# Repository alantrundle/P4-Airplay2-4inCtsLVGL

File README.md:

# P4-Airplay2-4inCtsLVGL
P4 Airplay2 Project featuring 4in TS and Capacitive TS

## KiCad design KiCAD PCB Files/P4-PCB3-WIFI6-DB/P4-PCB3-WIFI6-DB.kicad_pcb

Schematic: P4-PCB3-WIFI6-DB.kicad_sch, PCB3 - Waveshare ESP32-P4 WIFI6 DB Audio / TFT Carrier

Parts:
C1, C2: 220pF; C_0603_1608Metric; LCSC C1603; not fitted
C3, C7: 100uF; C_1206_3216Metric; LCSC C15008
C4: 4.7uF; C_0603_1608Metric; LCSC C19666
C5, C6, C10, C12, C14, C16, C17, C23, C25, C29, C30, C33, C34, C77, C86, C94, C95: 100nF; C_0603_1608Metric; LCSC C14663
C9, C11, C13, C15, C21, C32, C76: 10uF; C_0603_1608Metric; LCSC C19702
C24, C26, C89: 2.2uF; C_0603_1608Metric; LCSC C23630
C27, C28: 2.2nF; C_0603_1608Metric; LCSC C1604
C66, C81, C96: 10uF; C_0805_2012Metric; LCSC C15850
C87, C90, C91: 1uF; C_0603_1608Metric; LCSC C15849
C88: 22uF; C_0805_2012Metric; LCSC C45783
C92, C93: 100pF; C_0603_1608Metric; LCSC C14858
D1: Green LED; LED_0603_1608Metric; LCSC C12624
DS1: FH34SRJ-40S-0.5SH(50); ILI9488_40P_4inch_Checked; MPN FH34SRJ-40S-0.5SH(50); LCSC C506798
H1, H2, H3, H4: MountingHole; MountingHole_3.2mm_M3; not fitted
J2, J3: PJ-320D; HanElectricity_PJ320D_C22459515; LCSC C22459515
J6: DM3AT-SF-PEJM5; microSD_HC_Hirose_DM3AT-SF-PEJM5; LCSC C114218
J9: S5B-PH-SM4-TB(LF)(SN); JST_PH_S5B-PH-SM4-TB_1x05-1MP_P2.00mm_Horizontal; MPN S5B-PH-SM4-TB(LF)(SN); LCSC C265104
J10: S7B-PH-SM4-TB(LF)(SN); JST_PH_S7B-PH-SM4-TB_1x07-1MP_P2.00mm_Horizontal; MPN S7B-PH-SM4-TB(LF)(SN); LCSC C265453
J11: S8B-PH-SM4-TB(LF)(SN); JST_PH_S8B-PH-SM4-TB_1x08-1MP_P2.00mm_Horizontal; MPN S8B-PH-SM4-TB(LF)(SN); LCSC C265121
L1: 600R@100MHz Ferrite; L_0603_1608Metric; LCSC C107335
Q3: AO3400A; SOT-23; LCSC C20917
R1, R2: 4.7k; R_0603_1608Metric; LCSC C23162
R4: 10R; R_0603_1608Metric; LCSC C22859
R5, R6, R7, R8, R17: 33R; R_0603_1608Metric; LCSC C23140
R10, R11: 22R; R_0603_1608Metric; LCSC C23345
R12, R30, R31, R32, R34, R35, R46, R49, R50, R51: 10k; R_0603_1608Metric; LCSC C25804
R13, R14: 470R; R_0603_1608Metric; LCSC C23179
R15: 100R; R_0603_1608Metric; LCSC C22775
R16: 5.1k; R_0603_1608Metric; LCSC C23186
R23: 100k; R_0603_1608Metric; LCSC C25803
R26: 22R 0.5W; R_1210_3225Metric; LCSC C2960863
R47: 1k; R_0603_1608Metric; LCSC C21190
R48: 2k; R_0603_1608Metric; LCSC C22975
SW1: EM-01KP; SW_DIP_SPSTx01_Slide_6.7x4.1mm_W8.61mm_P2.54mm_LowProfile; LCSC C129077
TS1: FH34SRJ-6S-0.5SH(50); Hirose_FH34SRJ-6S-0.5SH_FT6236; MPN FH34SRJ-6S-0.5SH(50); LCSC C224194
U1: ESP32-P4-WIFI6-DB; Waveshare_P4_WIFI6_DB_Sockets; not fitted
U2: PCM5102APWR; TSSOP-20_4.4x6.5mm_P0.65mm; LCSC C107671
U3: ES8388; QFN-28-1EP_4x4mm_P0.45mm_EP2.6x2.6mm; LCSC C365736
U8: LD39150DT33-R; TO-252-3_TabPin2; LCSC C155559
U9: SN74LVC1G125DBVR; SOT-23-5; LCSC C23654

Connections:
/ADC_MIC_N: C91.2, C93.1, U3.23 (RIN1)
/ADC_MIC_P: C90.2, C92.1, U3.24 (LIN1)
/ES8388_3V3: C4.1, C5.1, C6.1, C17.2, C32.1, C33.1, C34.2, L1.2, R4.2, U3.2 (DVDD), U3.3 (PVDD), U3.16 (HPVDD)
/ES_ASDOUT: R5.2, U3.8 (ASDOUT)
/ES_AVDD: C11.1, C12.1, R4.1, R47.1, U3.17 (AVDD)
/ES_BCLK: R6.2, U3.5 (SCLK)
/ES_DSDIN: R7.2, U3.6 (DSDIN)
/ES_LRCK: R8.2, U3.7 (LRCK)
/ES_MCLK: R17.2, U3.1 (MCLK)
/ES_OUTL: R10.1, U3.12 (LOUT1)
/ES_OUTR: R11.1, U3.11 (ROUT1)
/GND: C1.2, C2.2, C4.2, C5.2, C6.2, C9.2, C10.2, C11.2, C12.2, C13.2, C14.2, C15.2, C16.2, C17.1, C21.2, C23.1, C25.1, C26.1, C27.1, C28.1, C29.1, C30.1, C32.2, C33.2, C34.1, C66.2, C76.2, C77.2, C81.2, C86.2, C87.1, C88.1, C89.2, C91.1, C92.2, C93.2, C94.2, C95.2, C96.2, D1.1 (K), DS1.5 (GND), DS1.16 (GND), DS1.37 (GND), J2.R2 (Ring_2), J3.R2 (Ring_2), J3.S (Sleeve), J6.6 (VSS), J6.9 (CD_A), J6.SH (SHIELD), J9.1 (GND), J10.1 (GND), J11.1 (GND), Q3.2 (S), R23.1, TS1.6 (GND), U1.3 (GND), U1.8 (GND), U1.13 (GND), U1.18 (GND), U1.23 (GND), U1.28 (GND), U1.33 (GND), U1.38 (GND), U2.3 (CPGND), U2.9 (AGND), U2.10 (DEMP), U2.11 (FLT), U2.12 (SCK), U2.16 (FMT), U2.19 (DGND), U3.4 (DGND), U3.13 (HPGND), U3.18 (AGND), U3.29 (EPAD), U8.2 (GND), U9.3 (GND)
/GPIO2: J10.7 (GPIO5(CS)), U1.15 (GPIO2)
/GPIO3: J11.4 (GPIO13), U1.14 (GPIO3)
/GPIO24: J11.5 (GPIO22), U1.19 (GPIO24)
/GPIO25: J11.6 (GPIO34), U1.20 (GPIO25)
/GPIO50: J11.8 (GPIO50), U1.9 (GPIO50)
/GPIO52: J11.7 (GPIO49), U1.1 (GPIO52)
/HEADSET_MIC: C90.1, J2.S (Sleeve), R48.2
/Headphone_L: C3.2, J2.T (Tip)
/Headphone_R: C7.2, J2.R1 (Ring_1)
/I2C_SCL: C2.1, J9.5 (GPIO8(SCL)), R1.2, TS1.3 (SCL), U1.16 (GPIO8), U3.28 (CCLK)
/I2C_SDA: C1.1, J9.4 (GPIO7(SDA)), R2.2, TS1.2 (SDA), U1.17 (GPIO7), U3.27 (CDATA)
/I2S_ASDOUT: R5.1, U1.29 (GPIO26)
/I2S_BCLK: R6.1, U1.34 (GPIO21)
/I2S_DSDIN: R7.1, U1.31 (GPIO23)
/I2S_LRCK: R8.1, U1.32 (GPIO22)
/I2S_MCLK: R17.1, U1.35 (GPIO20)
/LDO_3V3: C21.1, C23.2, C29.2, C30.2, C76.1, C77.1, C81.1, C86.1, C87.2, C88.2, C94.1, C95.1, DS1.6 (VDDI), DS1.7 (VDD), DS1.12 (RDX), DS1.38 (IM0), DS1.39 (IM1), DS1.40 (IM2), J6.4 (VDD), J9.3 (3.3V), J10.3 (3.3V), J11.3 (3.3V), L1.1, R1.1, R2.1, R12.1, R30.1, R31.1, R32.1, R34.1, R35.1, R46.1, R49.1, R50.1, R51.1, TS1.1 (VDD), U2.1 (CPVDD), U2.8 (AVDD), U2.20 (DVDD), U3.26 (CE), U8.3 (OUT), U9.5 (VCC)
/LED_K: DS1.34 (LED_K), DS1.35 (LED_K), DS1.36 (LED_K), Q3.3 (D)
/Lineout_L: C27.2, J3.T (Tip), R13.2
/Lineout_R: C28.2, J3.R1 (Ring_1), R14.2
/MIC_BIAS_FILTERED: C89.1, R47.2, R48.1
/MODULE_5V: C66.1, C96.1, J9.2 (5V), J10.2 (5V), J11.2 (5V), R16.1, R26.1, U1.39 (VSYS), U8.1 (IN)
/N_C3_Pad1: C3.1, R10.2
/N_C7_Pad1: C7.1, R11.2
/N_D1_A: D1.2 (A), R16.2
/N_DS1_LED_A: DS1.33 (LED_A), R26.2
/N_J6_CD_B: J6.10 (CD_B), R35.2, SW1.2
/N_Q3_G: Q3.1 (G), R15.2, R23.2
/N_U2_CAPM: C24.1, U2.4 (CAPM)
/N_U2_CAPP: C24.2, U2.2 (CAPP)
/N_U2_LDOO: C25.2, U2.18 (LDOO)
/N_U2_OUTL: R13.1, U2.6 (OUTL)
/N_U2_OUTR: R14.1, U2.7 (OUTR)
/N_U2_VNEG: C26.2, U2.5 (VNEG)
/N_U2_XSMT: R12.2, U2.17 (XSMT)
/N_U3_ADCVREF: C13.1, C14.1, U3.19 (ADCVREF)
/N_U3_VMID: C15.1, C16.1, U3.20 (VMID)
/N_U3_VREF: C9.1, C10.1, U3.10 (VREF)
/PCM_BCLK: U1.27 (GPIO27), U2.13 (BCK)
/PCM_DATA: U1.7 (GPIO28), U2.14 (DIN)
/PCM_LRCK: U1.6 (GPIO29), U2.15 (LRCK)
/SD1_D1: J6.8 (DAT1), R46.2
/SD1_D2: J6.1 (DAT2), R30.2
/SD_CS: J6.2 (DAT3/CD), R31.2, U1.10 (GPIO49)
/SD_DETECT: SW1.1, U1.2 (GPIO51)
/TCH_INT: TS1.4 (INT), U1.11 (GPIO5)
/TCH_RST: R50.2, TS1.5 (RST), U1.12 (GPIO4)
/TFT_BL: R15.1, U1.21 (GPIO48)
/TFT_CS: DS1.9 (CSX_SPI_CS), R49.2, U1.24 (GPIO46), U9.1
/TFT_DC: DS1.10 (DCX_SPI_DC), U1.25 (GPIO33)
/TFT_MISO: J6.7 (DAT0), J10.6 (GPIO4(MISO)), R34.2, U1.5 (GPIO30), U9.4
/TFT_MOSI: DS1.13 (SPI_MOSI), J6.3 (CMD), J10.5 (GPIO3(MOSI)), R32.2, U1.26 (GPIO32)
/TFT_RESET: DS1.15 (RESET), R51.2, U1.22 (GPIO47)
/TFT_SCK: DS1.11 (WRX_SPI_SCLK), J6.5 (CLK), J10.4 (GPIO2(SCK)), U1.4 (GPIO31)
/TFT_SDO_RAW: DS1.14 (SPI_MISO), U9.2

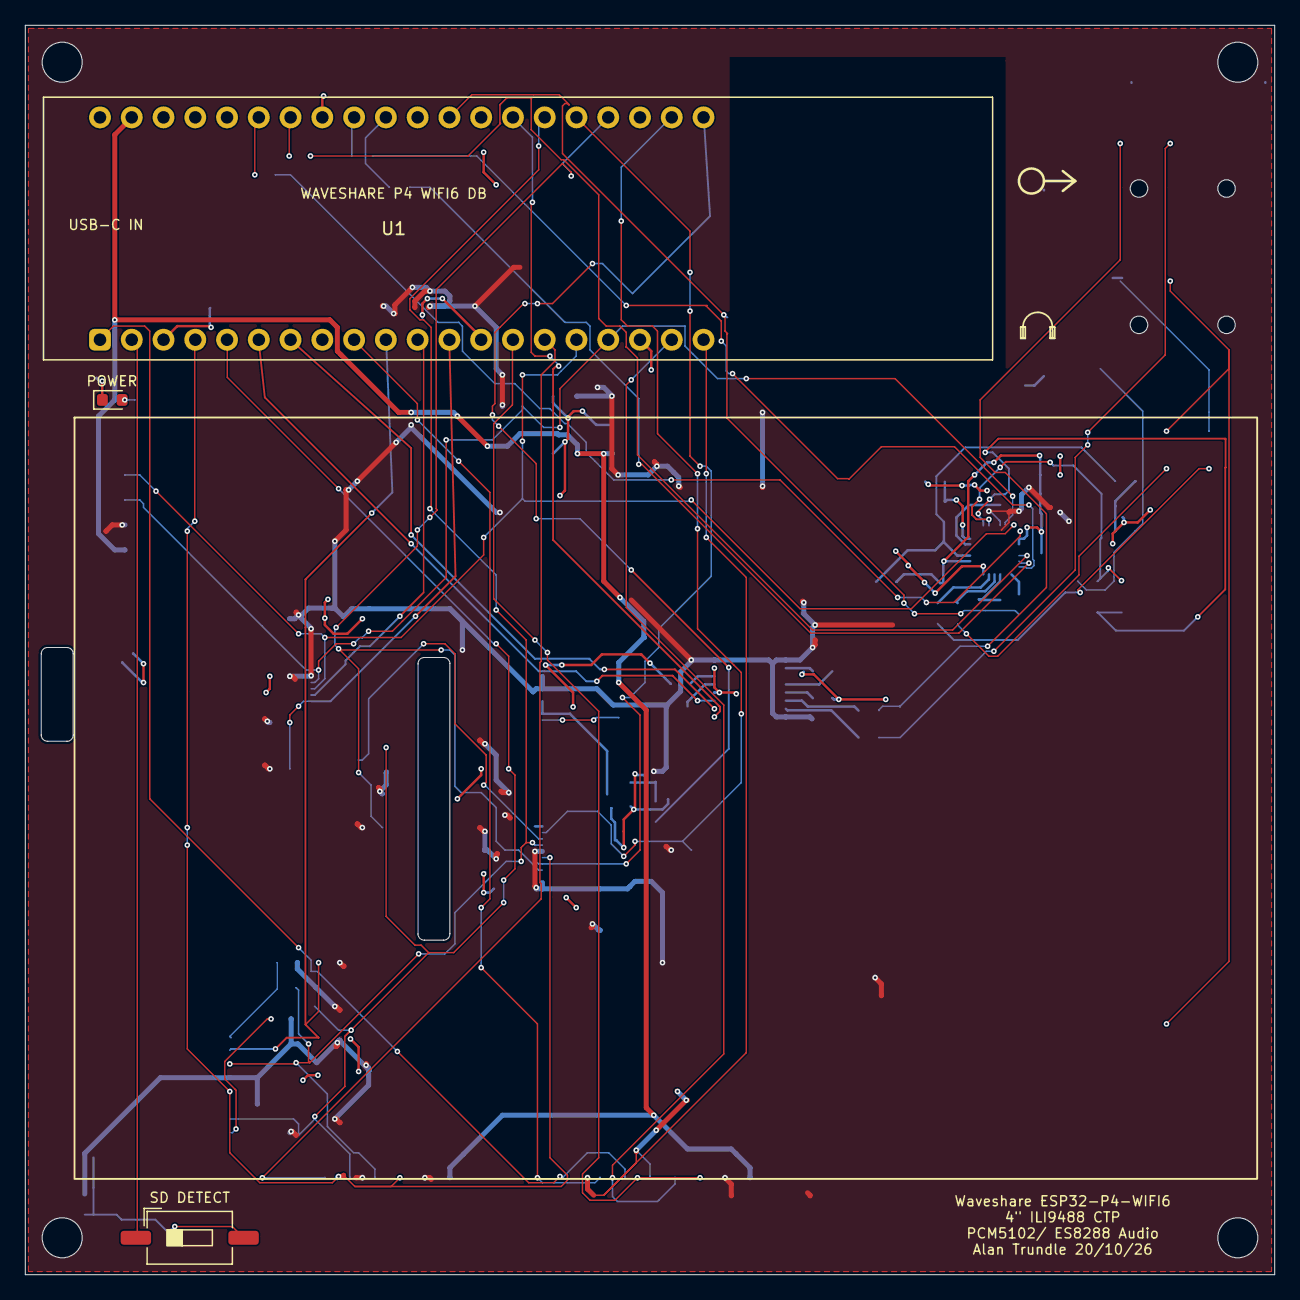
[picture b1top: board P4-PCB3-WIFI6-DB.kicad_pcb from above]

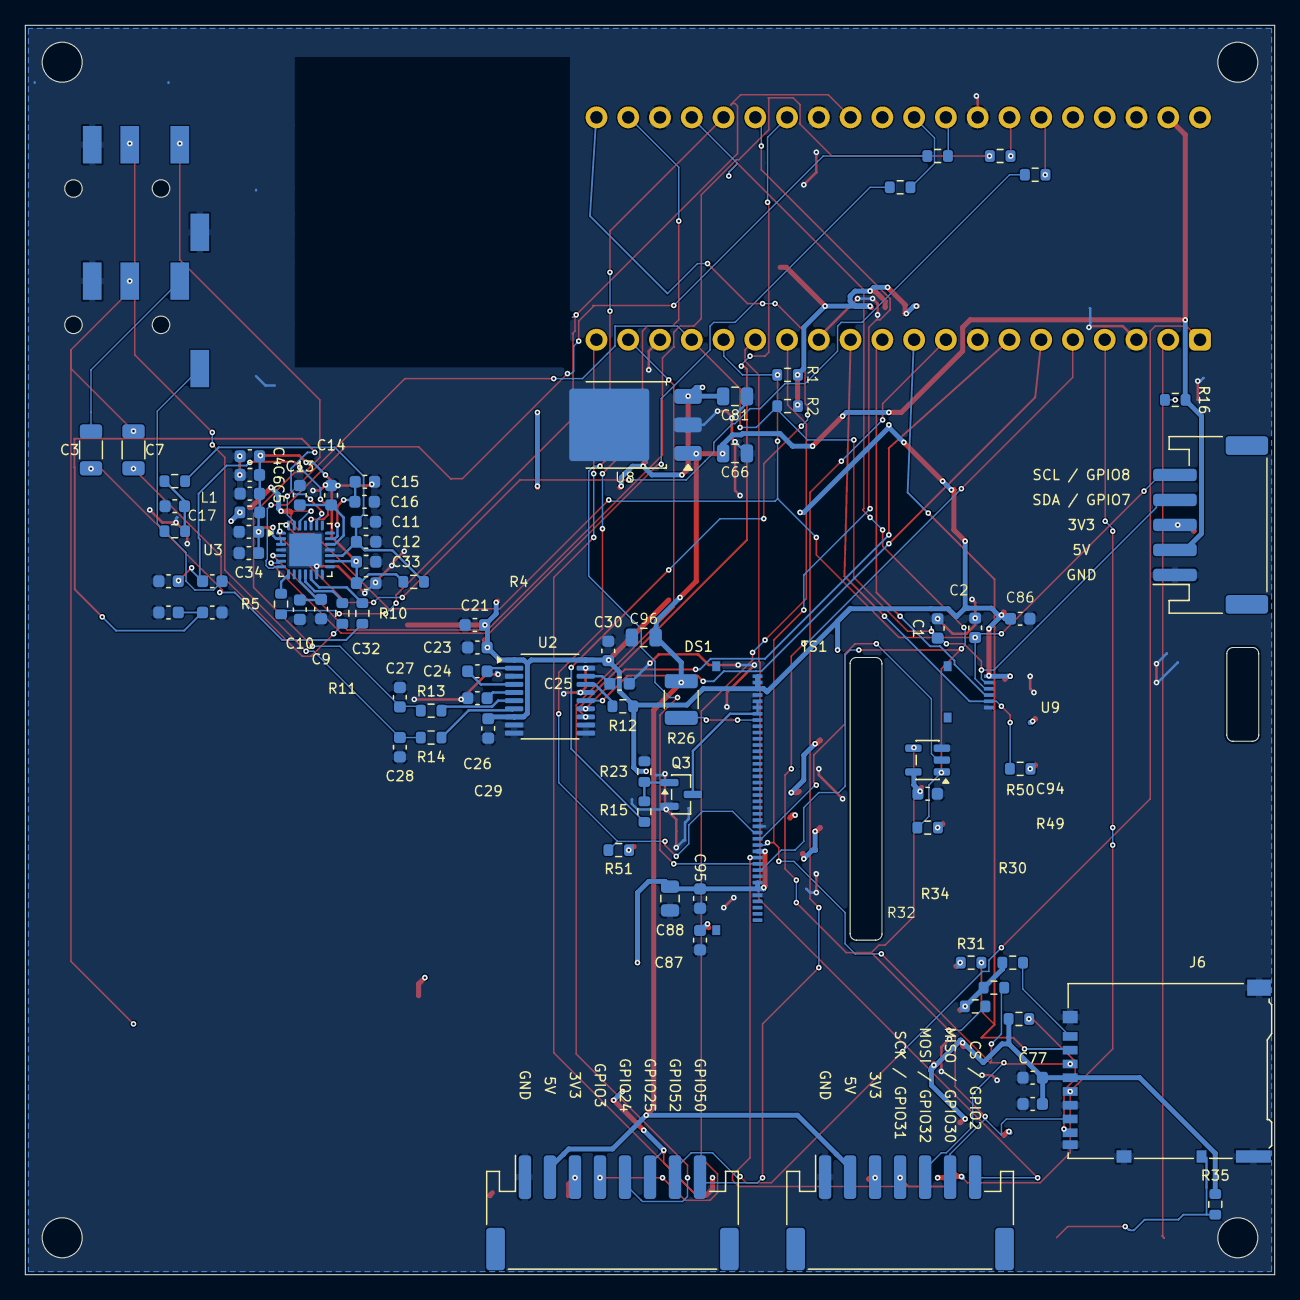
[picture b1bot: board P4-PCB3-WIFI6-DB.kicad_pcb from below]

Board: 2 copper layers, 99.9 x 99.9 mm, 92 parts (85 on the bottom side), 67 nets.

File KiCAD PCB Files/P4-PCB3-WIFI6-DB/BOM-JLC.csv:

"Comment","Designator","Footprint","LCSC Part #"
"100uF","C3,C7","P4Local_Capacitor_SMD:C_1206_3216Metric","C15008"
"4.7uF","C4","P4Local_Capacitor_SMD:C_0603_1608Metric","C19666"
"100nF","C5,C6,C10,C12,C14,C16,C17,C23,C25,C29,C30,C33,C34,C77,C86,C94,C95","P4Local_Capacitor_SMD:C_0603_1608Metric","C14663"
"10uF","C9,C11,C13,C15,C21,C32,C76","P4Local_Capacitor_SMD:C_0603_1608Metric","C19702"
"2.2uF","C24,C26,C89","P4Local_Capacitor_SMD:C_0603_1608Metric","C23630"
"2.2nF","C27,C28","P4Local_Capacitor_SMD:C_0603_1608Metric","C1604"
"10uF","C66,C81,C96","P4Local_Capacitor_SMD:C_0805_2012Metric","C15850"
"1uF","C87,C90,C91","P4Local_Capacitor_SMD:C_0603_1608Metric","C15849"
"22uF","C88","P4Local_Capacitor_SMD:C_0805_2012Metric","C45783"
"100pF","C92,C93","P4Local_Capacitor_SMD:C_0603_1608Metric","C14858"
"FH34SRJ-40S-0.5SH(50)","DS1","P4Local_Updated:ILI9488_40P_4inch_Checked","C506798"
"PJ-320D","J2,J3","P4Local_Connector_Audio_Han:HanElectricity_PJ320D_C22459515","C22459515"
"DM3AT-SF-PEJM5","J6","P4Local_Connector_Card:microSD_HC_Hirose_DM3AT-SF-PEJM5","C114218"
"S5B-PH-SM4-TB(LF)(SN)","J9","P4Local_Connector_JST:JST_PH_S5B-PH-SM4-TB_1x05-1MP_P2.00mm_Horizontal","C265104"
"S7B-PH-SM4-TB(LF)(SN)","J10","P4Local_Connector_JST:JST_PH_S7B-PH-SM4-TB_1x07-1MP_P2.00mm_Horizontal","C265453"
"S8B-PH-SM4-TB(LF)(SN)","J11","P4Local_Connector_JST:JST_PH_S8B-PH-SM4-TB_1x08-1MP_P2.00mm_Horizontal","C265121"
"600R@100MHz Ferrite","L1","P4Local_Inductor_SMD:L_0603_1608Metric","C107335"
"AO3400A","Q3","P4Local_Package_TO_SOT_SMD:SOT-23","C20917"
"4.7k","R1,R2","P4Local_Resistor_SMD:R_0603_1608Metric","C23162"
"10R","R4","P4Local_Resistor_SMD:R_0603_1608Metric","C22859"
"33R","R5,R6,R7,R8,R17","P4Local_Resistor_SMD:R_0603_1608Metric","C23140"
"22R","R10,R11","P4Local_Resistor_SMD:R_0603_1608Metric","C23345"
"10k","R12,R30,R31,R32,R34,R35,R46,R49,R50,R51","P4Local_Resistor_SMD:R_0603_1608Metric","C25804"
"470R","R13,R14","P4Local_Resistor_SMD:R_0603_1608Metric","C23179"
"100R","R15","P4Local_Resistor_SMD:R_0603_1608Metric","C22775"
"5.1k","R16","P4Local_Resistor_SMD:R_0603_1608Metric","C23186"
"100k","R23","P4Local_Resistor_SMD:R_0603_1608Metric","C25803"
"22R 0.5W","R26","P4Local_Resistor_SMD:R_1210_3225Metric","C2960863"
"1k","R47","P4Local_Resistor_SMD:R_0603_1608Metric","C21190"
"2k","R48","P4Local_Resistor_SMD:R_0603_1608Metric","C22975"
"FH34SRJ-6S-0.5SH(50)","TS1","P4Local_FT6236_TOUCH:Hirose_FH34SRJ-6S-0.5SH_FT6236","C224194"
"PCM5102APWR","U2","P4Local_Package_SO:TSSOP-20_4.4x6.5mm_P0.65mm","C107671"
"ES8388","U3","P4Local_Package_DFN_QFN:QFN-28-1EP_4x4mm_P0.45mm_EP2.6x2.6mm","C365736"
"LD39150DT33-R","U8","P4Local_Package_TO_SOT_SMD:TO-252-3_TabPin2","C155559"
"SN74LVC1G125DBVR","U9","P4Local_Package_TO_SOT_SMD:SOT-23-5","C23654"

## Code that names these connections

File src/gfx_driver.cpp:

#include <Arduino.h>
#include <LovyanGFX.hpp>

#include "gfx_driver.h"


LGFX_ST7796::LGFX_ST7796()
{
    // ============================================================
    // SPI BUS
    // ============================================================
    {
        auto cfg = _bus.config();

        cfg.spi_host = SPI2_HOST;
        cfg.spi_mode = 0;

        // Deliberately slow for initial display testing.
        cfg.freq_write = 40'000'000;
        cfg.freq_read  = 2000000;

        cfg.spi_3wire = false;
        cfg.use_lock  = true;

        // No DMA while debugging.
        cfg.dma_channel = 1;

        cfg.pin_sclk = TFT_SCLK;   // GPIO52
        cfg.pin_mosi = TFT_MOSI;   // GPIO51
        cfg.pin_miso = TFT_MISO;   // GPIO31
        cfg.pin_dc   = TFT_DC;     // GPIO39

        _bus.config(cfg);

        _panel.setBus(&_bus);
    }


    // ============================================================
    // ST7796 PANEL
    // ============================================================
    {
        auto cfg = _panel.config();

        cfg.pin_cs   = TFT_CS;      // GPIO30
        cfg.pin_rst  = TFT_RST;     // GPIO28
        cfg.pin_busy = -1;

        cfg.panel_width   = 320;
        cfg.panel_height  = 480;

        cfg.memory_width  = 320;
        cfg.memory_height = 480;

        cfg.offset_x = 0;
        cfg.offset_y = 0;

        cfg.offset_rotation = 0;

        cfg.readable = false;

        cfg.invert    = false;
        cfg.rgb_order = false;

        cfg.dlen_16bit = false;
        cfg.bus_shared = false;

        _panel.config(cfg);
    }


    // ============================================================
    // TOUCH
    // ============================================================
    {
        auto cfg = _touch.config();

        cfg.x_min = 0;
        cfg.y_min = 0;

        cfg.x_max = 319;
        cfg.y_max = 479;

        cfg.i2c_port = 1;
        cfg.i2c_addr = TOUCH_ADDR;

        cfg.pin_sda = I2C_SDA;
        cfg.pin_scl = I2C_SCL;

        cfg.pin_int = TOUCH_INT;
        cfg.pin_rst = TOUCH_RST;

        cfg.freq = 100000;

        _touch.config(cfg);

        _panel.setTouch(&_touch);
    }


    setPanel(&_panel);
}


bool LGFX_ST7796::readTouch(
    uint16_t &x,
    uint16_t &y,
    bool &pressed
)
{
    int32_t tx = 0;
    int32_t ty = 0;

    if (getTouch(&tx, &ty))
    {
        if (tx < 0) tx = 0;
        if (ty < 0) ty = 0;

        if (tx >= TFT_HOR_RES)
            tx = TFT_HOR_RES - 1;

        if (ty >= TFT_VER_RES)
            ty = TFT_VER_RES - 1;

        x = static_cast<uint16_t>(tx);
        y = static_cast<uint16_t>(ty);

        pressed = true;

        return true;
    }

    pressed = false;

    return false;
}


LGFX_ST7796 display;
